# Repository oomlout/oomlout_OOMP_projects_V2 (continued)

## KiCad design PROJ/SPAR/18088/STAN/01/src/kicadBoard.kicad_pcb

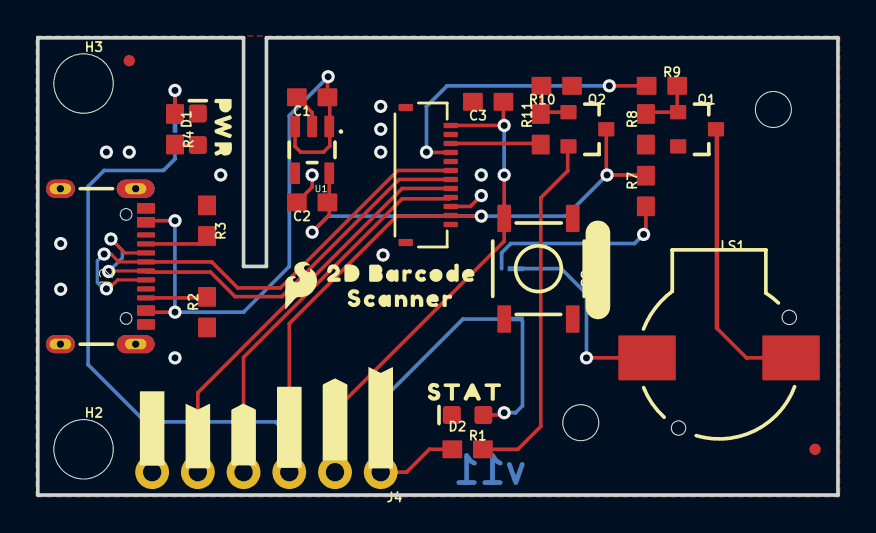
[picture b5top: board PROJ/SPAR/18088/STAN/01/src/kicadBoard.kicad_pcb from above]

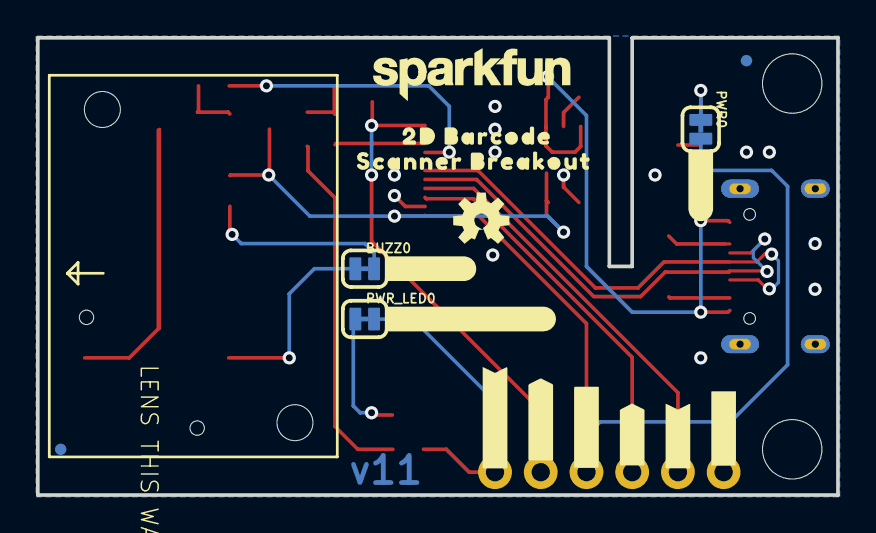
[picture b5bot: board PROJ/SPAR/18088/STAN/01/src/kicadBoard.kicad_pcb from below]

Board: 2 copper layers, 44.5 x 25.4 mm, 58 parts (19 on the bottom side), 22 nets.

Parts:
BUZZ0: JUMPER-SMT_2_NC_TRACE_SILK; SMT-JUMPER_2_NC_TRACE_SILK
C1, C2: 1.0uF; 0603
C3: 0.1uF; 0603
D1: RED; LED-0603
D2: GREEN; LED-0603
FD1, FD2, FD3, FD4: FIDUCIALUFIDUCIAL; FIDUCIAL-MICRO
FRAME1: FRAME-LETTER; CREATIVE_COMMONS
H2, H3: STAND-OFF
J2: USB-C-16P-2LAYER-PADS
J3: FPC_12_0.5MM
J4: 1X06_NO_SILK
LOGO1: OSHW-LOGOS; OSHW-LOGO-S
LOGO2: SFE_LOGO_FLAME.1_INCH; SFE_LOGO_FLAME_.1
LOGO3: SFE_LOGO_NAME.1_INCH; SFE_LOGO_NAME_.1
LS1: BUZZER-SMD; BUZZER-CCV
PWR0: JUMPER-SMT_2_NC_TRACE_SILK; SMT-JUMPER_2_NC_TRACE_SILK
PWR_LED0: JUMPER-SMT_2_NC_TRACE_SILK; SMT-JUMPER_2_NC_TRACE_SILK
Q1, Q2: 600mA/40V; SOT23-3
R1: 100; 0603
R2, R3: 5.1k; 0603
R4, R9, R11: 1k; 0603
R7: 10; 0603
R8, R10: 10k; 0603
S2: MOMENTARY-SWITCH-SPST-SMD-5.2MM-TALL; TACTILE_SWITCH_SMD_5.2MM
U1: 3.3V; SOT23-5
U2: BARCODE_SCANNER_MOUNT
U$1, U$7: ##TRIG##0
U$2, U$21: #STAT_#0
U$3: STAT0
U$4: #SCAN#0
U$5: #BUZZ#0
U$6: #STAT_LED#0
U$8: PWR0
U$9: #LED#0
U$17, U$18: 2D_BARCODE0
U$19: SCANNER0
U$20: SCANNER_BREAKOUT0
U$26, U$27: #TX_#0
U$28, U$29: #3#3V_#0
U$30, U$31: #RX_#0
U$32, U$33: #GND_#0

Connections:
3.3V: C2.1, J3.11, J4.3, PWR0.2, Q2.3, R7.2, U1.5
5V: C1.1, J2.VBUS1, J2.VBUS2, U1.1, U1.3
BUZZER: J3.4, R9.1
CC3: J2.A5, R3.2
CC4: J2.B5, R2.2
GND: C1.2, C2.2, C3.2, D1.C, D2.C, J2.GND, J2.GND2, J3.10, J4.6, Q1.2, R2.1, R3.1, R8.1, R10.1, S2.1, U1.2
unnamed: BUZZ0.2, R7.1
unnamed: LS1.-, Q1.3
unnamed: BUZZ0.1, LS1.+
unnamed: Q2.2, R1.2
unnamed: Q1.1, R8.2, R9.2
unnamed: PWR0.1, R4.1
unnamed: Q2.1, R10.2, R11.2
unnamed: D2.A, PWR_LED0.1
unnamed: D1.A, R4.2
RXI: J3.9, J4.4
STATUS_LED: J3.3, R11.1
STATUS_OUT: J4.1, PWR_LED0.2, R1.1
TXO: J3.8, J4.5
USB_N: J2.A7, J2.B7, J3.7
USB_P: J2.A6, J2.B6, J3.6
~SCAN_TRIGGER: C3.1, J3.1, J4.2, S2.3

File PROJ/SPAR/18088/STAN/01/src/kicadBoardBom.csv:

"Id";"Designator";"Package";"Quantity";"Designation";"Supplier and ref";
1;"Q1,Q2";"SOT23-3";2;"600mA/40V";;;
2;"R7";"0603";1;"10";;;
3;"LS1";"BUZZER-CCV";1;"BUZZER-SMD";;;
4;"R11,R9,R4";"0603";3;"1k";;;
5;"D2";"LED-0603";1;"GREEN";;;
6;"FD2,FD1,FD4,FD3";"FIDUCIAL-MICRO";4;"FIDUCIALUFIDUCIAL";;;
7;"D1";"LED-0603";1;"RED";;;
8;"R10,R8";"0603";2;"10k";;;
9;"C2,C1";"0603";2;"1.0uF";;;
10;"U$1,U$7";"##TRIG##0";2;"";;;
11;"U$8";"PWR0";1;"";;;
12;"J4";"1X06_NO_SILK";1;"";;;
13;"U$26,U$27";"#TX_#0";2;"";;;
14;"S2";"TACTILE_SWITCH_SMD_5.2MM";1;"MOMENTARY-SWITCH-SPST-SMD-5.2MM-TALL";;;
15;"R3,R2";"0603";2;"5.1k";;;
16;"J3";"FPC_12_0.5MM";1;"";;;
17;"U$4";"#SCAN#0";1;"";;;
18;"U$30,U$31";"#RX_#0";2;"";;;
19;"U$2,U$21";"#STAT_#0";2;"";;;
20;"J2";"USB-C-16P-2LAYER-PADS";1;"";;;
21;"U$32,U$33";"#GND_#0";2;"";;;
22;"H3,H2";"STAND-OFF";2;"STAND-OFF";;;
23;"U1";"SOT23-5";1;"3.3V";;;
24;"LOGO2";"SFE_LOGO_FLAME_.1";1;"SFE_LOGO_FLAME.1_INCH";;;
25;"C3";"0603";1;"0.1uF";;;
26;"U$17,U$18";"2D_BARCODE0";2;"";;;
27;"U$19";"SCANNER0";1;"";;;
28;"U$28,U$29";"#3#3V_#0";2;"";;;
29;"R1";"0603";1;"100";;;
30;"U$3";"STAT0";1;"";;;
31;"FRAME1";"CREATIVE_COMMONS";1;"FRAME-LETTER";;;
32;"PWR0,BUZZ0,PWR_LED0";"SMT-JUMPER_2_NC_TRACE_SILK";3;"JUMPER-SMT_2_NC_TRACE_SILK";;;
33;"LOGO1";"OSHW-LOGO-S";1;"OSHW-LOGOS";;;
34;"LOGO3";"SFE_LOGO_NAME_.1";1;"SFE_LOGO_NAME.1_INCH";;;
35;"U$9";"#LED#0";1;"";;;
36;"U$5";"#BUZZ#0";1;"";;;
37;"U$20";"SCANNER_BREAKOUT0";1;"";;;
38;"U$6";"#STAT_LED#0";1;"";;;
39;"U2";"BARCODE_SCANNER_MOUNT";1;"BARCODE_SCANNER_MOUNT";;;

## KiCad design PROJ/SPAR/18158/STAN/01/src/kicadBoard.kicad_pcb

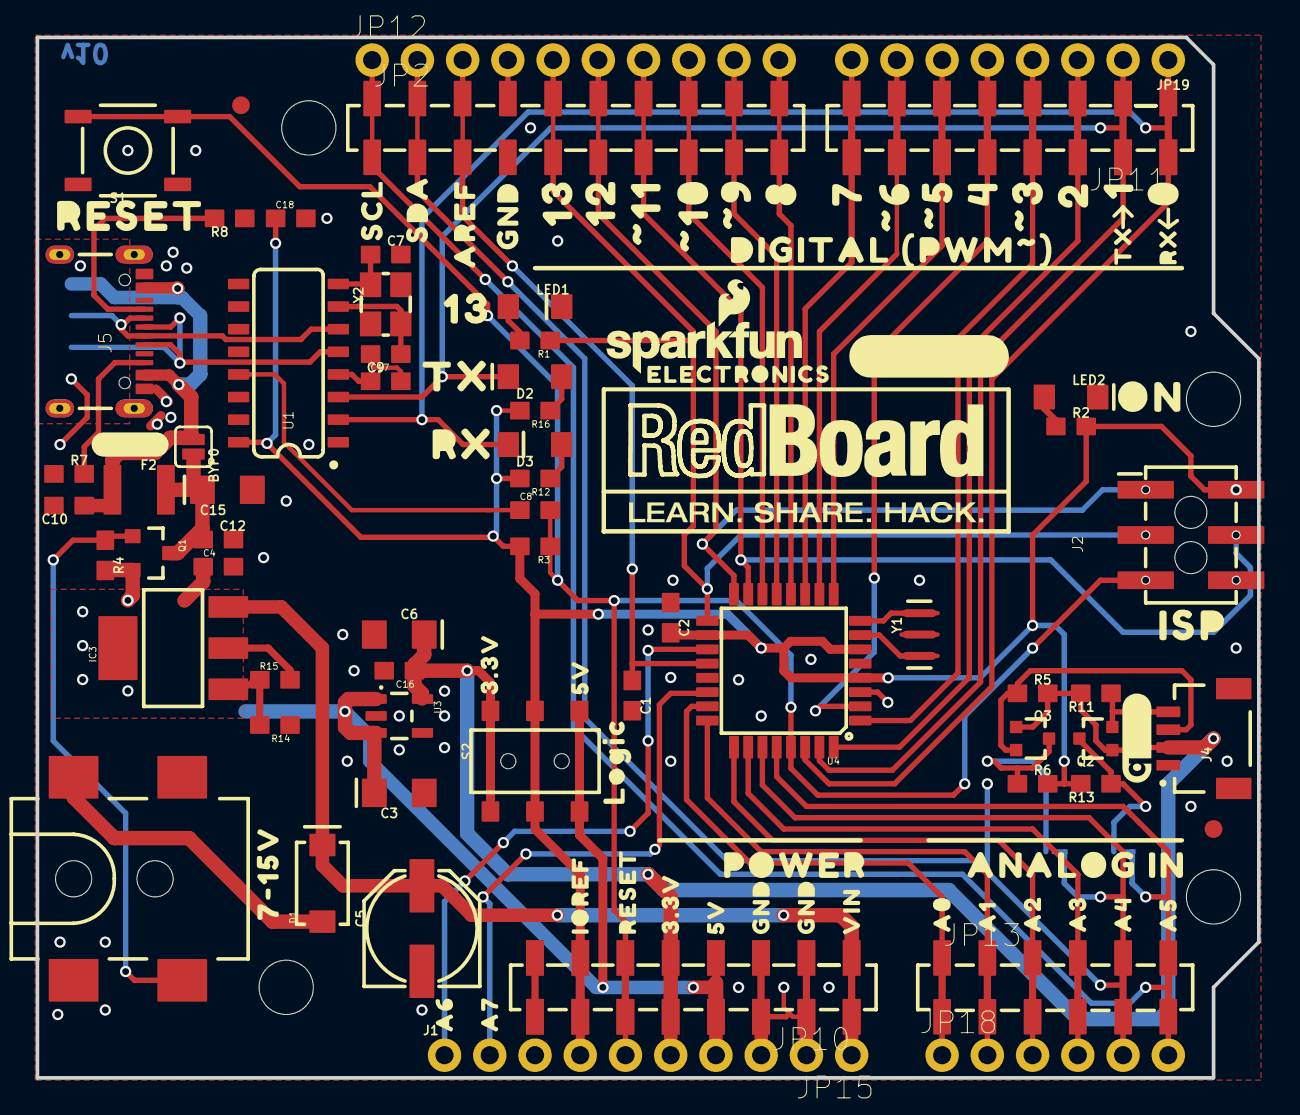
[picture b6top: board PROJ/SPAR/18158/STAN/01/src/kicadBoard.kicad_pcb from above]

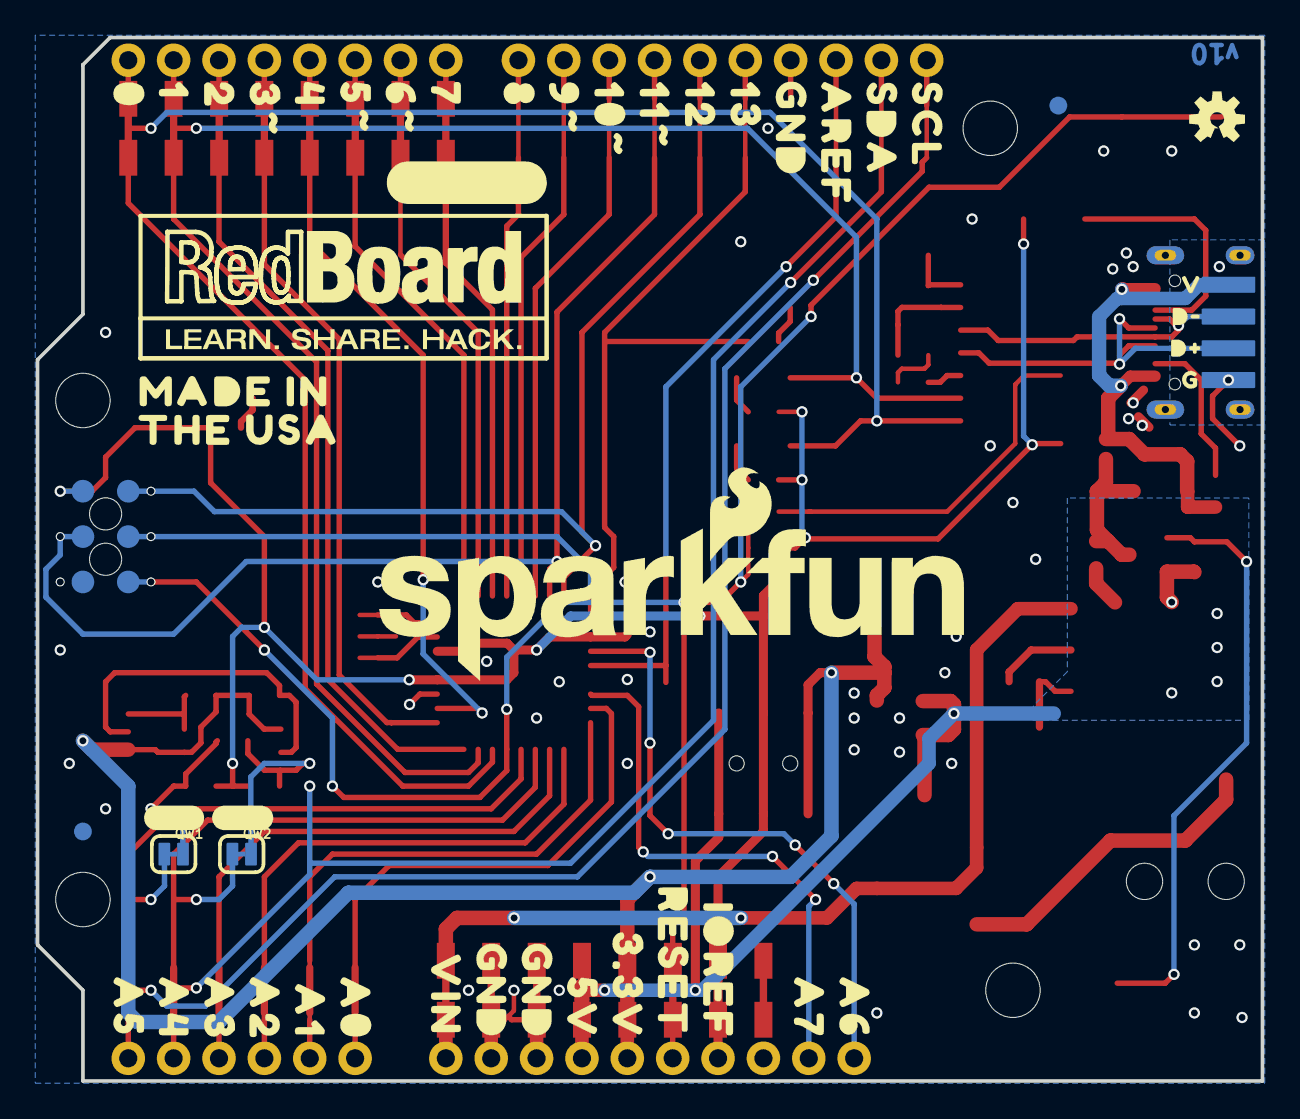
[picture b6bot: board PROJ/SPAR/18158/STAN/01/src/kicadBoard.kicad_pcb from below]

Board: 2 copper layers, 68.6 x 58.4 mm, 179 parts (57 on the bottom side), 53 nets.

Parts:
BYP0: JUMPER-SMT_2_NO_SILK; SMT-JUMPER_2_NO_SILK
C1, C2, C4, C8, C10, C12, C18: 0.1uF; 0603
C3, C6, C15: 10uF; EIA3216
C5: 47uF; PANASONIC_D
C7, C9: 10pF; 0603
C16: 1.0uF; 0603
C17: 10nF; 0603
D1: 1A/40V/500mV; SMA-DIODE
D2: GREEN; LED-1206
D3: YELLOW; LED-1206-HIDDENSILK
F2: 6V/2A; 1210
FD1, FD2: FIDUCIAL1X2; FIDUCIAL-1X2
FRAME1: FRAME-LEDGER; CREATIVE_COMMONS
IC3: LM1117; SOT223
J1: DNP; 1X02_NO_SILK
J2: ISP; 2X3_SMT_POSTS
J3: 5.5x2.1mm Barrel; POWER_JACK_SMD
J4: QWIIC_RIGHT_ANGLE; JST04_1MM_RA
J5: USB Female Type C Connector; USB-C-16P-2LAYER-PADS
JP1: SFE_LOGO_NAME.1_INCH; SFE_LOGO_NAME_.1
JP2: 1X10_SMD_COMBINED
JP3, JP4, JP5, JP6: STAND-OFFTIGHT; STAND-OFF-TIGHT
JP7: SFE_LOGO_FLAME.1_INCH; SFE_LOGO_FLAME_.1
JP8, JP9: FIDUCIAL1X2; FIDUCIAL-1X2
JP10: 1X08_SMD_COMBINED
JP11: JP11; 1X08_SMD_COMBINED
JP12: DNP; 1X10_NO_SILK
JP13: 1X06_SMD_STRAIGHT_COMBO
JP14: USB_SOLDER_PADS; USB-SOLDER-PADS
JP15, JP19: DNP; 1X08_NO_SILK
JP18: DNP; 1X06_NO_SILK
LED1: Blue; LED-1206-HIDDENSILK
LED2: GREEN; LED-1206
LOGO1: QWIIC_LOGO_5MM; QWIIC_5MM
Q1: 20V/4.2A/52mΩ/1.4W; SOT23-3
Q2, Q3: 310mA/60V/1.6Ω; SOT323
QW1, QW2: JUMPER-SMT_2_NC_TRACE_SILK; SMT-JUMPER_2_NC_TRACE_SILK
R1, R12, R16: 4.7k; 0603
R2, R3, R4: 10k; 0603
R5, R6, R11, R13: 2.2k; 0603
R7, R8: 5.1k; 0603
R14: 715; 0603
R15: 240; 0603
S1: Tall Switch; TACTILE_SWITCH_SMD_5.2MM
S2: SWITCH_DPDT_SMD_AYZ0202
TP1, TP2, TP3, TP4, TP5, TP6: TP-3x5; PAD.03X.05
U1: CH340G; SO016
U3: 3.3V; SOT23-5
U4: ATMEGA328P_TQFP; TQFP32-08
U$1, U$3: REDBOARD_LOGO
U$2: _D#0
U$4: V0
U$9: 10#0
U$10: G0
U$11: LOGIC0
U$12: D#0
U$13, U$95: _RESET0
U$14: #BYP#0
U$16: OSHW-LOGOS; OSHW-LOGO-S
U$17: 7#15V0
U$18: _AREF0
U$19: _SCL0
U$20: _SDA0
U$21: 11#0
U$22, U$77: 130
U$23, U$76: 120
U$24: #110
U$25: #100
U$26: #90
U$27, U$72: 80
U$28, U$71: 70
U$29: #60
U$30: #50
U$31, U$68: 40
U$32: #30
U$33, U$66: 20
U$34, U$65: 10
U$35, U$64: 00
U$36: TX0
U$37: RX0
U$38: DIGITAL_##PWM####_0
U$39: 13_0
U$40: _TX0
U$41: _RX0
U$42: _GND0
U$43, U$51: 3#3V0
U$44, U$52: 5V0
U$45: ON0
U$46: ISP0
U$47: POWER0
U$48: ANALOG_IN0
U$49: IOREF0
U$50: RESET0
U$53, U$54: GND0
U$55: VIN0
U$56: A00
U$57: A10
U$58: A20
U$59: A30
U$60: A40
U$61: A50
U$62: A60
U$63: A70
U$67: 3#0
U$69: 5#0
U$70: 6#0
U$73: 9#0
U$78: SFE_LOGO_NAME_.3
U$79: AREF0
U$80: SDA0
U$81: SCL0
U$82: MADE_IN0
U$83: THE_USA0
U$84: _A40
U$85, U$99, U$107: _GND_0
U$86: _A30
U$87: _A20
U$88: _A10
U$89: _A00
U$90: _VIN0
U$93: _5V0
U$94: _3#3V0
U$96: _IOREF0
U$97: _A60
U$98: _A70
U$100, U$103: #PLUS#0
U$101: SFE_LOGO_FLAME_.2
U$102: _A50
U$104: ELECTRONICS0
U$105: #A4#0
U$106: #A5#0
Y1: 16MHz; RESONATOR-SMD-3.2X1.3
Y2: 12MHz; CRYSTAL-SMD-3.2X2.5MM

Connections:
3.3V: C6.+, C16.1, J4.2, JP10.5, JP15.5, Q2.1, Q3.1, R5.2, R11.2, S2.1, S2.4, U3.5
5V: C3.+, C4.1, IC3.2, IC3.4, JP10.4, JP15.4, Q1.2, R4.2, R15.2, S2.3, S2.6, U3.1, U3.3
A0: JP13.1, JP18.1, U4.23
A1: JP13.2, JP18.2, U4.24
A2: JP13.3, JP18.3, U4.25
A3: JP13.4, JP18.4, U4.26
A4/SDA: JP2.2A, JP2.2B, JP12.2, JP13.5, JP18.5, QW2.1, U4.27
A5/SCL: JP2.1A, JP2.1B, JP12.1, JP13.6, JP18.6, QW1.1, U4.28
A6: J1.1, U4.19
A7: J1.2, U4.22
AREF: C1.1, JP2.3A, JP2.3B, JP12.3, U4.20
CC1: J5.A5, R8.2
CC2: J5.B5, R7.2
CIPO: J2.1, JP2.6A, JP2.6B, JP12.6, TP4.P$1, U4.16
COPI: J2.4, JP2.7A, JP2.7B, JP12.7, TP2.P$1, U4.15
D2: JP11.3, JP19.3, U4.32
D3: JP11.4, JP19.4, U4.1
D4: JP11.5, JP19.5, U4.2
D5: JP11.6, JP19.6, U4.9
D6: JP11.7, JP19.7, U4.10
D7: JP11.8, JP19.8, U4.11
D8: JP2.10A, JP2.10B, JP12.10, U4.12
D9: JP2.9A, JP2.9B, JP12.9, U4.13
D10: JP2.8A, JP2.8B, JP12.8, U4.14
D+: J5.A6, J5.B6, JP14.D+, U1.5
D-: J5.A7, J5.B7, JP14.D-, U1.6
GND: C1.2, C2.1, C3.-, C4.2, C5.-, C6.-, C7.2, C9.2, C10.2, C12.2, C15.-, C16.2, C17.2, C18.2, J2.6, J3.GND, J4.1, J5.GND, J5.GND2, JP2.4A, JP2.4B, JP10.2, JP10.3, JP12.4, JP14.GND, JP15.2, JP15.3, LED1.C, LED2.C, R7.1, R8.1, R14.1, S1.1, S1.2, TP3.P$1, U1.1, U3.2, U4.3, U4.5, U4.21, Y1.2, Y2.2, Y2.4
INSERT: J3.P$4, Q1.1, R4.1
LV_SCL: J4.4, Q2.2, R11.1
LV_SDA: J4.3, Q3.2, R5.1
unnamed: LED1.A, R1.2
unnamed: LED2.A, R2.1
unnamed: U4.7, Y1.1
unnamed: U4.8, Y1.3
unnamed: D2.A, R16.1
unnamed: C17.1, U1.4
unnamed: Q2.3, QW1.2, R13.1
unnamed: C9.1, U1.7, Y2.1
unnamed: D3.A, R12.1
unnamed: C7.1, U1.8, Y2.3
unnamed: IC3.1, R14.2, R15.1
unnamed: Q3.3, QW2.2, R6.1
PWRIN: D1.A, J3.VIN0
RX-I: D3.C, JP11.1, JP19.1, U1.2, U4.30
SCK: J2.3, JP2.5A, JP2.5B, JP12.5, R1.1, TP5.P$1, U4.17
SHLD: J5.SHLD1, J5.SHLD2, J5.SHLD3, J5.SHLD4
TX-O: D2.C, JP11.2, JP19.2, U1.3, U4.31
USBVCC: BYP0.2, C12.1, C15.+, F2.2, Q1.3
VCC: C2.2, C18.1, J2.2, JP10.7, JP15.7, R2.2, R3.2, R6.2, R12.2, R13.2, R16.2, S2.2, S2.5, TP1.P$1, U1.16, U4.4, U4.6, U4.18
VIN: C5.+, D1.C, IC3.3, JP10.1, JP15.1
VUSB: BYP0.1, C10.1, F2.1, J5.VBUS1, J5.VBUS2, JP14.VBUS
~DTR: C8.1, U1.13
~RESET: C8.2, J2.5, JP10.6, JP15.6, R3.1, S1.3, S1.4, TP6.P$1, U4.29

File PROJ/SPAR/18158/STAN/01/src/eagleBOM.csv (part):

"Part";"Value";"Device";"Package";"Description";"DESIGNER";"PROD_ID";"REV";"SF_ID";"SF_SKU";"VALUE";
"BYP";"JUMPER-SMT_2_NO_SILK";"JUMPER-SMT_2_NO_SILK";"SMT-JUMPER_2_NO_SILK";"Normally open jumper";"";"";"";"";"";"";
"C1";"0.1uF";"0.1UF-0603-25V-(+80/-20%)";"0603";"0.1µF ceramic capacitors";"";"CAP-00810";"";"";"";"0.1uF";
"C2";"0.1uF";"0.1UF-0603-25V-(+80/-20%)";"0603";"0.1µF ceramic capacitors";"";"CAP-00810";"";"";"";"0.1uF";
"C3";"10uF";"10UF-POLAR-EIA3216-16V-10%(TANT)";"EIA3216";"10.0µF polarized capacitors";"";"CAP-00811";"";"";"";"10uF";
"C4";"0.1uF";"0.1UF-0603-25V-(+80/-20%)";"0603";"0.1µF ceramic capacitors";"";"CAP-00810";"";"";"";"0.1uF";
"C5";"47uF";"47UF-POLAR-PANASONIC_D-35V-20%";"PANASONIC_D";"47µF polarized capacitors";"";"CAP-08478";"";"";"";"47uF";
"C6";"10uF";"10UF-POLAR-EIA3216-16V-10%(TANT)";"EIA3216";"10.0µF polarized capacitors";"";"CAP-00811";"";"";"";"10uF";
"C7";"10pF";"10PF-0603-50V-5%";"0603";"10pF ceramic capacitors";"";"CAP-11812";"";"";"";"10pF";
"C8";"0.1uF";"0.1UF-0603-25V-(+80/-20%)";"0603";"0.1µF ceramic capacitors";"";"CAP-00810";"";"";"";"0.1uF";
"C9";"10pF";"10PF-0603-50V-5%";"0603";"10pF ceramic capacitors";"";"CAP-11812";"";"";"";"10pF";
"C10";"0.1uF";"0.1UF-0603-25V-(+80/-20%)";"0603";"0.1µF ceramic capacitors";"";"CAP-00810";"";"";"";"0.1uF";
"C12";"0.1uF";"0.1UF-0603-25V-(+80/-20%)";"0603";"0.1µF ceramic capacitors";"";"CAP-00810";"";"";"";"0.1uF";
"C15";"10uF";"10UF-POLAR-EIA3216-16V-10%(TANT)";"EIA3216";"10.0µF polarized capacitors";"";"CAP-00811";"";"";"";"10uF";
"C16";"1.0uF";"1.0UF-0603-16V-10%";"0603";"1µF ceramic capacitors";"";"CAP-00868";"";"";"";"1.0uF";
"C17";"10nF";"10NF-0603-50V-10%";"0603";"0.01uF/10nF/10,000pF ceramic capacitors";"";"CAP-00867";"";"";"";"10nF";
"C18";"0.1uF";"0.1UF-0603-25V-(+80/-20%)";"0603";"0.1µF ceramic capacitors";"";"CAP-00810";"";"";"";"0.1uF";
"D1";"1A/40V/500mV";"DIODE-SCHOTTKY-SS14";"SMA-DIODE";"Schottky diode";"";"DIO-08053";"";"";"";"1A/40V/500mV";
"D2";"GREEN";"LED-GREENLILYPAD";"LED-1206";"Green SMD LED";"";"DIO-09910";"";"";"";"GREEN";
"D3";"YELLOW";"LED-YELLOW_HIDDENSILK";"LED-1206-HIDDENSILK";"Yellow SMD LED";"";"DIO-09909";"";"";"";"YELLOW";
"F2";"6V/2A";"PPTC_6V2A";"1210";"Resettable Fuse PPTC";"";"RES-14313";"";"";"";"6V/2A";
"FD1";"FIDUCIAL1X2";"FIDUCIAL1X2";"FIDUCIAL-1X2";"Fiducial Alignment Points";"";"";"";"";"";"";
"FD2";"FIDUCIAL1X2";"FIDUCIAL1X2";"FIDUCIAL-1X2";"Fiducial Alignment Points";"";"";"";"";"";"";
"FRAME1";"FRAME-LEDGER";"FRAME-LEDGER";"CREATIVE_COMMONS";"Schematic Frame - Ledger";"";"";"";"";"";"";
"IC3";"LM1117";"V_REG_LM1117SOT223";"SOT223";"Voltage Regulator LM1117";"";"VREG-08170";"";"";"";"";
"J1";"DNP";"CONN_021X02_NO_SILK";"1X02_NO_SILK";"Multi connection point. Often used as Generic Header-pin footprint for 0.1 inch spaced/style header connections";"";"";"";"";"";"";
"J2";"ISP";"AVR_SPI_PROG_3X2SMD";"2X3_SMT_POSTS";"AVR ISP 6 Pin";"";"CONN-11415";"";"";"";"";
"J3";"5.5x2.1mm Barrel";"POWER_JACKSMD";"POWER_JACK_SMD";"Power Jack Connector";"";"CONN-08106";"";"PRT-12748";"";"5.5x2.1mm Barrel";
"J4";"QWIIC_RIGHT_ANGLE";"QWIIC_CONNECTORJS-1MM";"JST04_1MM_RA";"SparkFun I2C Standard Qwiic Connector";"";"CONN-13694";"";"";"";"QWIIC_RIGHT_ANGLE";
"J5";"USB Female Type C Connector";"USB_C_2-LAYER_PADS";"USB-C-16P-2LAYER-PADS";"USB Type C 16Pin Connector";"";"CONN-14122";"";"";"";"";
"JP1";"SFE_LOGO_NAME.1_INCH";"SFE_LOGO_NAME.1_INCH";"SFE_LOGO_NAME_.1";"SparkFun Font Logo";"";"";"";"";"";"";
"JP2";"";"CONN_10SMD_COMBO-FEMALE";"1X10_SMD_COMBINED";"Multi connection point. Often used as Generic Header-pin footprint for 0.1 inch spaced/style header connections";"";"CONN-11219";"";"";"";"";
"JP3";"STAND-OFFTIGHT";"STAND-OFFTIGHT";"STAND-OFF-TIGHT";"Stand Off";"";"";"";"";"";"";
"JP4";"STAND-OFFTIGHT";"STAND-OFFTIGHT";"STAND-OFF-TIGHT";"Stand Off";"";"";"";"";"";"";
"JP5";"STAND-OFFTIGHT";"STAND-OFFTIGHT";"STAND-OFF-TIGHT";"Stand Off";"";"";"";"";"";"";
"JP6";"STAND-OFFTIGHT";"STAND-OFFTIGHT";"STAND-OFF-TIGHT";"Stand Off";"";"";"";"";"";"";
"JP7";"SFE_LOGO_FLAME.1_INCH";"SFE_LOGO_FLAME.1_INCH";"SFE_LOGO_FLAME_.1";"SparkFun Flame Logo";"";"";"";"";"";"";
"JP8";"FIDUCIAL1X2";"FIDUCIAL1X2";"FIDUCIAL-1X2";"Fiducial Alignment Points";"";"";"";"";"";"";
"JP9";"FIDUCIAL1X2";"FIDUCIAL1X2";"FIDUCIAL-1X2";"Fiducial Alignment Points";"";"";"";"";"";"";
"JP10";"";"CONN_08SMD-COMBO-FEMALE";"1X08_SMD_COMBINED";"Multi connection point. Often used as Generic Header-pin footprint for 0.1 inch spaced/style header connections";"";"CONN-10204";"";"PRT-11543";"";"";
"JP11";"JP11";"CONN_08SMD-COMBO-FEMALE";"1X08_SMD_COMBINED";"Multi connection point. Often used as Generic Header-pin footprint for 0.1 inch spaced/style header connections";"";"CONN-10204";"";"PRT-11543";"";"";
"JP12";"DNP";"CONN_10NO_SILK_PTH_FEMALE";"1X10_NO_SILK";"Multi connection point. Often used as Generic Header-pin footprint for 0.1 inch spaced/style header connections";"";"CONN-11219";"";"";"";"";
"JP13";"";"CONN_06SMD-STRAIGHT-COMBO-FEMALE";"1X06_SMD_STRAIGHT_COMBO";"Multi connection point. Often used as Generic Header-pin footprint for 0.1 inch spaced/style header connections";"";"CONN-10203";"";"";"";"";
"JP14";"USB_SOLDER_PADS";"USB_SOLDER_PADS";"USB-SOLDER-PADS";"Solder pad access to USB pins. Helpful to expose on PCBs so user can attach external USB connector if necessary.";"";"";"";"";"";"";
"JP15";"DNP";"CONN_08NO_SILK_DNP";"1X08_NO_SILK";"Multi connection point. Often used as Generic Header-pin footprint for 0.1 inch spaced/style header connections";"";"CONN-10204";"";"";"";"";
"JP18";"DNP";"CONN_06NO_SILK_NO_POP";"1X06_NO_SILK";"Multi connection point. Often used as Generic Header-pin footprint for 0.1 inch spaced/style header connections";"";"CONN-10203";"";"";"";"";
"JP19";"DNP";"CONN_08NO_SILK_DNP";"1X08_NO_SILK";"Multi connection point. Often used as Generic Header-pin footprint for 0.1 inch spaced/style header connections";"";"";"";"";"";"";
"LED1";"Blue";"LED-BLUE_HIDDENSILK";"LED-1206-HIDDENSILK";"Blue SMD LED";"";"DIO-09911";"";"";"";"";
"LED2";"GREEN";"LED-GREENLILYPAD";"LED-1206";"Green SMD LED";"";"DIO-09910";"";"";"";"GREEN";
"LOGO1";"QWIIC_LOGO_5MM";"QWIIC_LOGO_5MM";"QWIIC_5MM";"Qwiic Logos for placement on schematic and PCB. The 5.5mm silk logo is best for placing next to Qwiic connector.";"";"";"";"";"";"";
"Q1";"20V/4.2A/52mΩ/1.4W";"MOSFET_PCH-DMG2305UX-7";"SOT23-3";"P-channel MOSFETs";"";"TRANS-14388";"";"";"";"20V/4.2A/52mΩ/1.4W";
"Q2";"310mA/60V/1.6Ω";"MOSFET-NCH-2N7002PW";"SOT323";"N-channel MOSFETs";"";"TRANS-11151";"";"";"";"310mA/60V/1.6Ω";
"Q3";"310mA/60V/1.6Ω";"MOSFET-NCH-2N7002PW";"SOT323";"N-channel MOSFETs";"";"TRANS-11151";"";"";"";"310mA/60V/1.6Ω";
"QW1";"JUMPER-SMT_2_NC_TRACE_SILK";"JUMPER-SMT_2_NC_TRACE_SILK";"SMT-JUMPER_2_NC_TRACE_SILK";"Normally closed trace jumper";"";"";"";"";"";"";
"QW2";"JUMPER-SMT_2_NC_TRACE_SILK";"JUMPER-SMT_2_NC_TRACE_SILK";"SMT-JUMPER_2_NC_TRACE_SILK";"Normally closed trace jumper";"";"";"";"";"";"";
"R1";"4.7k";"4.7KOHM-0603-1/10W-1%";"0603";"4.7kΩ resistor";"";"RES-07857";"";"";"";"4.7k";
"R2";"10k";"10KOHM-0603-1/10W-1%";"0603";"10kΩ resistor";"";"RES-00824";"";"";"";"10k";
"R3";"10k";"10KOHM-0603-1/10W-1%";"0603";"10kΩ resistor";"";"RES-00824";"";"";"";"10k";
"R4";"10k";"10KOHM-0603-1/10W-1%";"0603";"10kΩ resistor";"";"RES-00824";"";"";"";"10k";
"R5";"2.2k";"2.2KOHM-0603-1/10W-1%";"0603";"2.2kΩ resistor";"";"RES-08272";"";"";"";"2.2k";
"R6";"2.2k";"2.2KOHM-0603-1/10W-1%";"0603";"2.2kΩ resistor";"";"RES-08272";"";"";"";"2.2k";
"R7";"5.1k";"5.1KOHM5.1KOHM-0603-1/10W-1%";"0603";"";"";"RES-12083";"";"";"";"5.1k";
"R8";"5.1k";"5.1KOHM5.1KOHM-0603-1/10W-1%";"0603";"";"";"RES-12083";"";"";"";"5.1k";
"R11";"2.2k";"2.2KOHM-0603-1/10W-1%";"0603";"2.2kΩ resistor";"";"RES-08272";"";"";"";"2.2k";
"R12";"4.7k";"4.7KOHM-0603-1/10W-1%";"0603";"4.7kΩ resistor";"";"RES-07857";"";"";"";"4.7k";
"R13";"2.2k";"2.2KOHM-0603-1/10W-1%";"0603";"2.2kΩ resistor";"";"RES-08272";"";"";"";"2.2k";
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
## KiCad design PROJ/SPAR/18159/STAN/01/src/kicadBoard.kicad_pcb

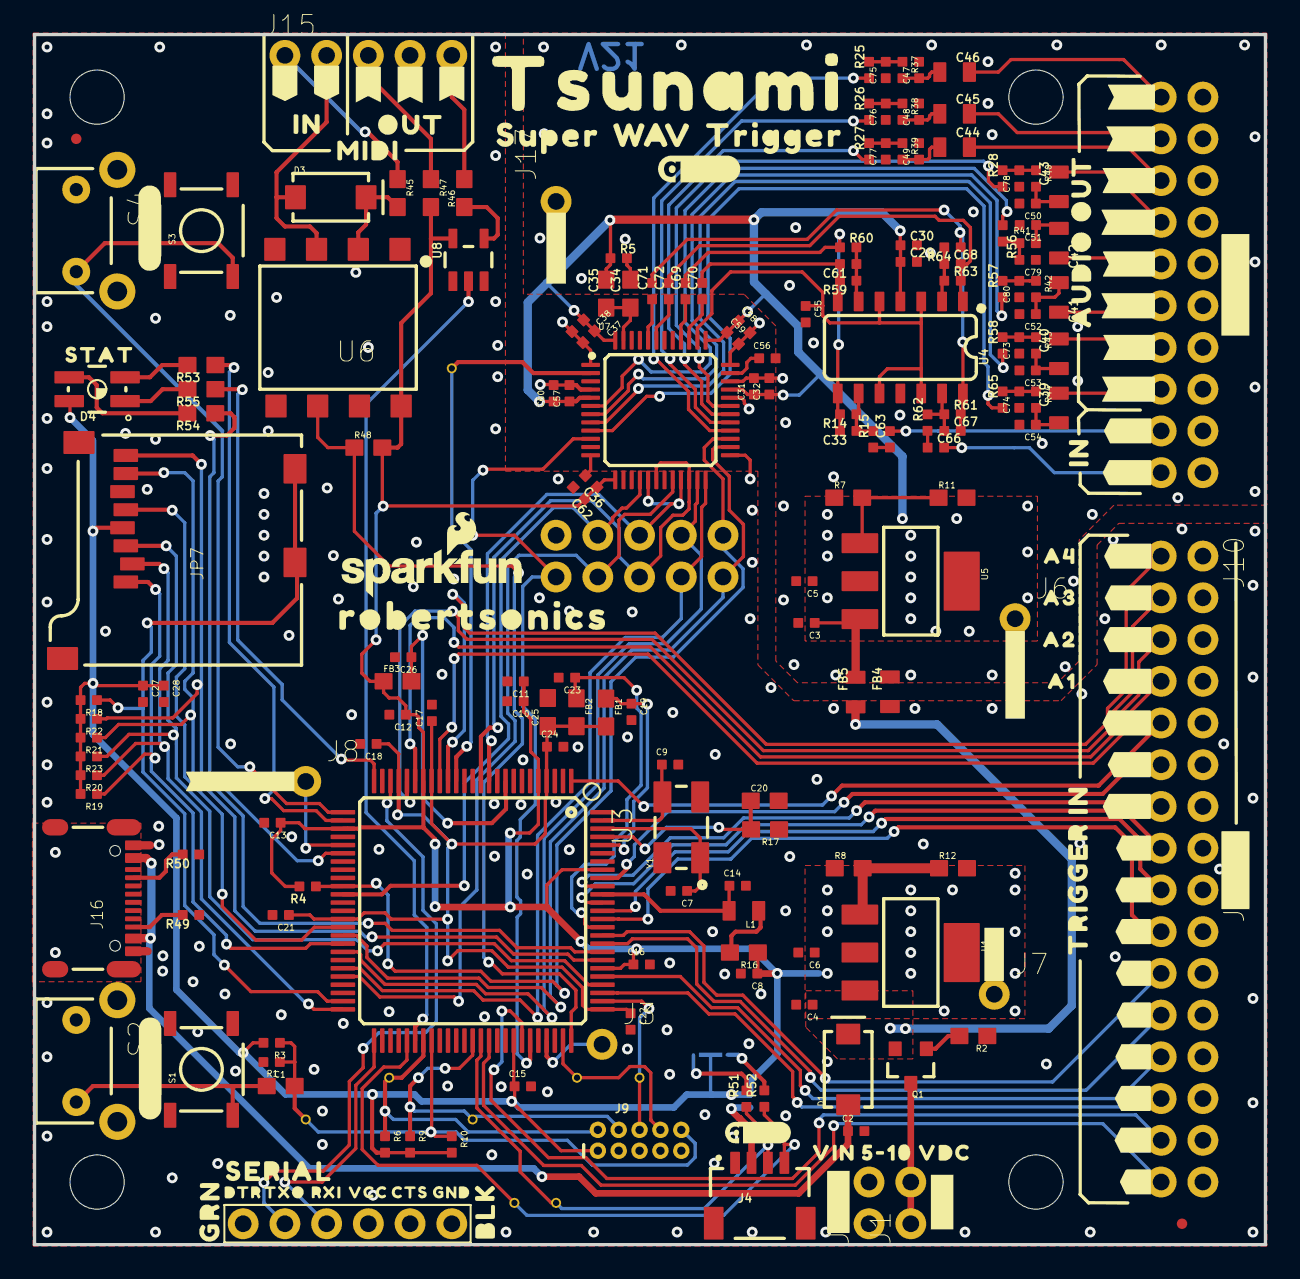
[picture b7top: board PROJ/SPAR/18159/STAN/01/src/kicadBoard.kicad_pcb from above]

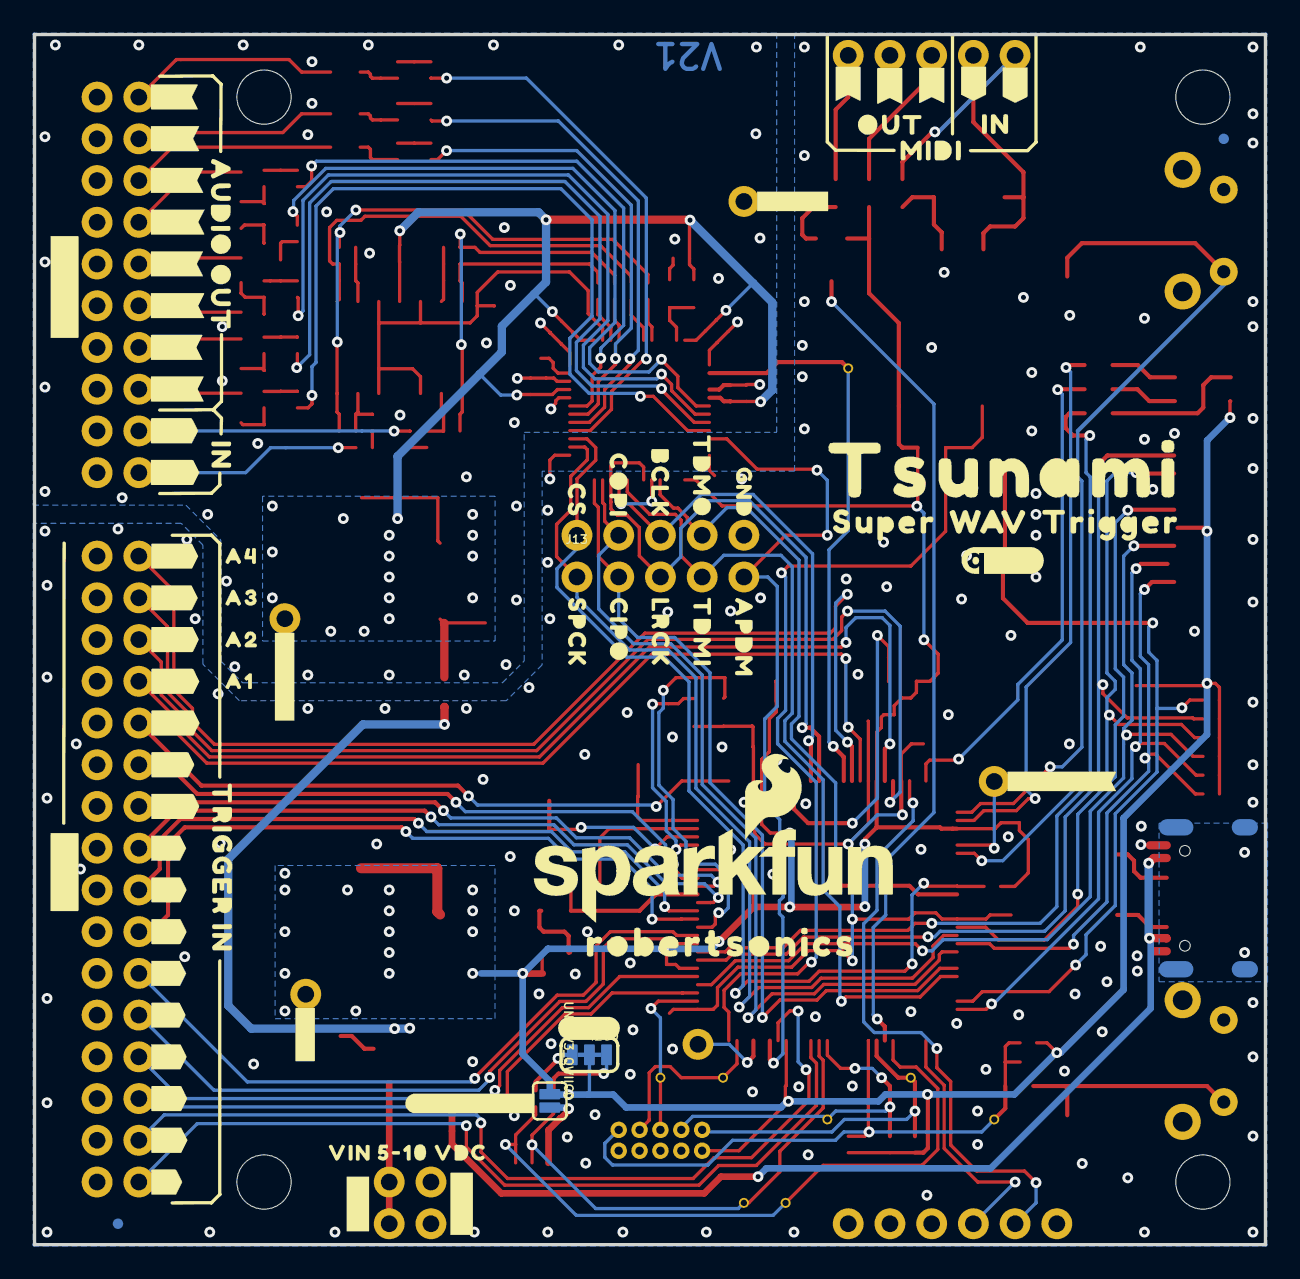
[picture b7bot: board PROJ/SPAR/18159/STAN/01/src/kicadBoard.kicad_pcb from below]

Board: 2 copper layers, 74.9 x 73.7 mm, 327 parts (76 on the bottom side), 138 nets.

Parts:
C1: 10nF; 0402-TIGHT
C2, C5, C6, C11, C27: 10uF; 0402-TIGHT
C3, C4, C8, C10, C12, C13, C15, C16, C17, C18, C19, C21, C22, C23, C24, C26, C28, C29, C31, C36, C37, C47, C48, C49, C50, C51, C52, C53, C54, C55, C56, C57, C59, C73, C74, C75, C76, C77, C78, C79, C80: 0.1uF; 0402-TIGHT
C7, C9: 12pF; 0402-TIGHT
C14: 4.7uF; 0402-TIGHT
C20: 10pF; 0603
C25: 2.2uF; 0603
C30, C32, C38, C58, C60, C62, C63, C66, C69, C70, C71, C72: 1.0uF; 0402-TIGHT
C33, C61, C67, C68: 100pF; 0402-TIGHT
C34: 5.6nF; 0603
C35: 390nF; 0603
C39, C40, C41, C42, C43, C44, C45, C46: 22uF; 0805
D1, D3: 1A/40V/500mV; SMA-DIODE
D4: RGB; P-LCC-4-3
FB1, FB2, FB3: 470Ω; 0603
FB4, FB5: 600Ω; 0805
FD1, FD2, FD3, FD4: FIDUCIALUFIDUCIAL; FIDUCIAL-MICRO
FRAME1, FRAME2: FRAME-LEDGER; CREATIVE_COMMONS
H1, H2, H3, H4: STAND-OFF
I2C0: SMT-JUMPER_3_2-NC_TRACE_SILK
J1: VDC-IN; 1X02_NO_SILK
J2: GND-IN; 1X02_NO_SILK
J3: DEBUG; 1X01_NO_SILK
J4: QWIIC; JST04_1MM_RA
J6: 3.3VA; 1X01_NO_SILK
J7: 3.3V; 1X01_NO_SILK
J8: PLAYING; 1X01_NO_SILK
J9: CORTEX_JTAG_DEBUG_PTH_NS; 2X5-PTH-1.27MM-NO_SILK
J10: TRIG2; 2X8_NOSILK
J11: TRIG1; 2X8_NOSILK
J13: 2X5_NOSILK
J14: AUDIO I/O; 2X10_NOSILK
J15: MIDI; 1X05_NO_SILK
J16: USB-C; USB-C-16P-4LAYER-ISOLATED
J17: AGND; 1X01_NO_SILK
J18: 6_PIN_SERIAL_TARGET_SIDE_W_SILK
JP7: USD-SOCKETNEW; MICRO-SD-SOCKET-PP
L1: 10μH; 0805
LOGO2: SFE_LOGO_NAME_FLAME.2_INCH; SFE_LOGO_NAME_FLAME_.2
LOGO3: QWIIC_LOGO_4MM; QWIIC_4MM
Q1: 3.1A/30V/105mΩ; SOT23-3
R1: 33; 0603
R2: 1M; 0603
R3, R4, R18, R23: 10k; 0402-TIGHT
R5: 560Ω; 0402-TIGHT
R6, R9, R10, R19, R20, R21, R22: 100k; 0402-TIGHT
R7, R8: 390; 0603
R11, R12: 240; 0603
R14, R15, R59, R60, R61, R62, R63, R64: 33k; 0402-TIGHT
R16: 2.2; 0603
R17: 5.62k; 0603
R25, R26, R27, R28, R37, R38, R39, R40, R41, R42, R43, R44, R56, R57, R58, R65: 10Ω; 0402-TIGHT
R45, R46, R47, R48, R55: 220; 0603
R49, R50: 5.1k; 0402-TIGHT
R51, R52: 2.2k; 0402-TIGHT
R53, R54: 100; 0603
S1: Reset; TACTILE_SWITCH_SMD_5.2MM
S2, S4: DNP; TACTILE_SWITCH_PTH_RIGHT_ANGLE
S3: User; TACTILE_SWITCH_SMD_5.2MM
TP1: I2C_SCK; TP_15TH
TP2: I2C_SDA; TP_15TH
TP4: MCLK; TP_15TH
TP5: SWDIO/TMS; TP_15TH
TP6: SWCK/TCK; TP_15TH
TP7: TDO; TP_15TH
TP8: TDI; TP_15TH
TP9: NRESET; TP_15TH
U1, U5: LM1117; SOT223
U3: ATSAMS70N20A-AN; LQFP100
U4: LMV324; SO14
U6: 6N138M; 8-SMD
U7: ADAU1328; LQFP-48
U8: 74AHC1G125W5-7; SOT23-5
U$3: GND_0
U$4, U$73: QWIIC_5MM
U$5: STAT0
U$6: #USER#0
U$7: #RESET#0
U$8, U$9: ROBERTSONICS0
U$10, U$167: #2L#0
U$11: #1L#0
U$12, U$120: #1R#0
U$13: #2R#0
U$14: #3R#0
U$15: #3L#0
U$16: #4L#0
U$17: #4R#0
U$18: #4#3
U$19: #2#5
U$20, U$107: AUDIO_OUT0
U$21, U$46, U$108, U$123: IN0
U$22, U$106: TRIGGER_IN0
U$23, U$85: #GND#0
U$24: #1#0
U$25: SERIAL3
U$26, U$60: SUPER0
U$27, U$99: VIN_5#10_VDC0
U$28, U$84: #AGND#0
U$29: #2#0
U$30: #3#0
U$31, U$56, U$117: #4#0
U$32, U$58, U$118: #5#0
U$33: #6#0
U$34: #7#0
U$35: #8#0
U$36: #9#0
U$37: #10#0
U$38: #11#0
U$39: #12#0
U$40: #PLAYING#30
U$41, U$112: #3V3#0
U$43: #13#0
U$44: #3V3_A#0
U$45, U$122: MIDI0
U$47, U$124: OUT0
U$48: #14#0
U$49: #15#0
U$50: #16#0
U$51: A10
U$52: A20
U$53: A30
U$54: A40
U$55: #5#6
U$57: #2#6
U$59: #4#6
U$61, U$110: #GND#1
U$62, U$68: TRIGGER0
U$63, U$69: TSUNAMI0
U$64, U$70: W0
U$65, U$71: A0
U$66, U$72: V0
U$67, U$111: #VIN#2
U$74: #16#5
U$75: #15#17
U$76: #14#17
U$77: #13#17
U$78: #12#17
U$79: #11#17
U$80: #10#17
U$81: #9#17
U$82: #8#17
U$83: #7#17
U$86: CS17
U$87: BCLK19
U$88: COPI18
U$89: TDMO20
U$91: SPCK22
U$92: TDMI25
U$93: LRCK24
U$94: CIPO23
U$95: APDM26
U$96: #AGND#27
U$97: #AGND#28
U$98: #PLAYING#29
U$102: A117
U$103: A2118
U$104: A32119
U$105: A432120
U$113: #I2C#6
U$116: #1L#3
U$119: #1L#6
U$121: #1R#2
U$141: SFE_LOGO_NAME_FLAME_.1
U$162: #3V3_A#4
U$163: #3V3_QWIIC#0
U$164: #1R#3
U$165: #5#5
U$166: #1L#2
U$168: #2R#3
U$169: #3L#3
U$170: #3R#4
U$171: #4L#4
U$172: #4R#5
U$173: #6#17
U$174: #5#17
U$175: #4#17
U$176: #3#17
U$177: #2#17
U$178: #1#17
UNK3V3_QWIIC0: SMT-JUMPER_2_NO_SILK
Y1: 11.2896 MHz; CRYSTAL-OSC-SMD-5X3

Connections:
3.3V: C6.1, C8.1, C10.1, C11.1, C12.1, C13.1, C15.1, C16.1, C27.1, C28.1, C36.1, C62.1, D4.4, FB3.1, I2C0.2, J7.1, J9.1, JP7.VCC, R3.2, R4.2, R6.2, R9.2, R10.2, R12.2, R16.1, R18.2, R19.2, R20.2, R21.2, R22.2, R23.2, R47.2, R48.2, U1.2, U1.4, U3.5, U3.19, U3.28, U3.68, U3.81, U3.93, U6.8, U7.13, U8.5, UNK3V3_QWIIC0.1
56: D3.C, R45.2, U6.2
ADC1LN: C69.1, U7.40
ADC1LP: C70.1, U7.39
ADC2LN: C71.1, U7.44
ADC2LP: C72.1, U7.43
AGND: C3.2, C5.2, C29.2, C30.2, C31.2, C32.2, C37.2, C38.2, C47.2, C48.2, C49.2, C50.2, C51.2, C52.2, C53.2, C54.2, C55.2, C56.2, C57.2, C58.2, C59.2, C60.2, C73.1, C74.1, C75.1, C76.1, C77.1, C78.1, C79.1, C80.1, FB4.2, J14.2, J14.4, J14.6, J14.8, J14.10, J14.12, J14.14, J14.16, J14.18, J14.20, J17.1, R7.1, U4.11, U7.1, U7.4, U7.32, U7.34, U7.36
AIN1L: C63.2, J14.17
AIN1R: C66.2, J14.19
AOUT1L: C46.1, C47.1, R37.2
AOUT1R: C45.1, C48.1, R38.2
AOUT2L: C44.2, J14.5
AOUT2R: C43.1, C50.1, R40.2
AOUT3L: C42.2, J14.9
AOUT3R: C41.1, C52.1, R42.2
AOUT4L: C40.1, C53.1, R43.2
AOUT4R: C39.1, C54.1, R44.2
APDN: J13.9, U3.70, U7.10
BCLK: J13.6, U3.11, U7.17, U7.21
BLUE_LED: R54.1, U3.31
CC1: J16.A5, R50.2
CC2: J16.B5, R49.2
CM_1.5V: C55.1, U4.3, U4.5, U4.10, U4.12, U7.38
DBUG: J3.1, U3.72
DGND: C1.2, C2.2, C4.2, C6.2, C7.2, C8.2, C9.2, C10.2, C11.2, C12.2, C13.2, C14.2, C15.2, C16.2, C17.2, C18.2, C19.2, C20.2, C21.2, C22.2, C23.2, C24.2, C25.2, C26.2, C27.2, C28.2, C36.2, C62.2, FB4.1, J2.1, J2.2, J4.1, J9.3, J9.5, J9.9, J10.2, J10.4, J10.6, J10.8, J10.10, J10.12, J10.14, J10.16, J11.2, J11.4, J11.6, J11.8, J11.10, J11.12, J11.14, J11.16, J13.10, J15.4, J16.GND, J16.GND2, J18.6, JP7.GND, JP7.GND1, JP7.GND3, R2.1, R8.1, R17.1, R49.1, R50.1, S1.1, S2.1, S3.1, S4.1, U3.3, U3.6, U3.7, U3.8, U3.10, U3.29, U3.67, U6.5, U7.12, U7.25, U8.1, U8.3, Y1.2, Y1.4
GREEN_LED: R53.1, U3.27
I2C_SCK: J4.4, R52.1, TP1.1, U3.55
I2C_SDA: J4.3, R51.1, TP2.1, U3.64
LF: C34.1, C35.1, U7.47
LRCK: J13.5, U3.12, U7.18, U7.22
MCLK: TP4.1, U3.15, U7.2
MIDI-IN-PIN4: J15.1, R45.1
MIDI-IN-PIN5: D3.A, J15.2, U6.3
MIDI-OUT-PIN4: J15.3, R47.1
MIDI-OUT-PIN5: J15.5, R46.2
MIN: R48.1, U3.75, U6.6
MOUT: U3.56, U8.2
unnamed: C7.1, U3.98, Y1.1
unnamed: C9.1, U3.99, Y1.3
unnamed: C19.1, FB1.1, U3.96
unnamed: C14.1, L1.2, U3.90
unnamed: C23.1, FB2.1, U3.86
unnamed: C33.2, C69.2, R14.2, R60.1, U4.8
unnamed: I2C0.3, R51.2
unnamed: J8.1, U3.30
unnamed: I2C0.1, R52.2
unnamed: C34.2, R5.2
unnamed: C63.1, R15.1
unnamed: C61.2, C70.2, R59.2, U4.7
unnamed: C68.2, C72.2, R63.2, U4.1
unnamed: C20.1, R17.2, U3.97
unnamed: C26.1, FB3.2, U3.9
unnamed: C39.2, J14.15
unnamed: C40.2, J14.13
unnamed: C41.2, J14.11
unnamed: C42.1, C51.1, R41.2
unnamed: C43.2, J14.7
unnamed: C75.2, R25.2, R37.1
unnamed: L1.1, R16.2
unnamed: R7.2, R11.1, U5.1
unnamed: R1.1, S1.3, S2.2
unnamed: C74.2, R44.1, R65.2
unnamed: C73.2, R43.1, R58.2
unnamed: R8.2, R12.1, U1.1
unnamed: C80.2, R42.1, R57.2
unnamed: C44.1, C49.1, R39.2
unnamed: C46.2, J14.1
unnamed: C45.2, J14.3
unnamed: J4.2, UNK3V3_QWIIC0.2
unnamed: D4.2, R53.2
unnamed: D4.3, R54.2
unnamed: D4.1, R55.2
unnamed: R46.1, U8.4
unnamed: C3.1, FB5.2, U5.3
unnamed: C56.1, U7.35
unnamed: C61.1, R59.1, R60.2, U4.6
unnamed: C33.1, R14.1, R15.2, U4.9
unnamed: C79.2, R41.1, R56.2
unnamed: C78.2, R28.2, R40.1
unnamed: C76.2, R26.2, R38.1
unnamed: C77.2, R27.2, R39.1
unnamed: C67.2, C71.2, R61.2, R64.1, U4.14
unnamed: C66.1, R62.1
unnamed: C68.1, R63.1, R64.2, U4.2
unnamed: C67.1, R61.1, R62.2, U4.13
unnamed: Q1.1, R2.2
NRESET: C1.1, J9.10, R1.2, R3.1, R10.1, TP9.1, U3.58
OL1: R25.1, U7.28
OL2: R27.1, U7.30
OL3: R56.1, U7.6
OL4: R58.1, U7.8
OR1: R26.1, U7.29
OR2: R28.1, U7.31
OR3: R57.1, U7.7
OR4: R65.1, U7.9
RED_LED: R55.1, U3.25
REGINPUTS: C4.1, D1.C, FB5.1, Q1.2, U1.3
RXD: J18.3, U3.51
SDCD: JP7.CD1, JP7.CD2, R18.1, U3.49
SDCLK: JP7.SCLK, U3.40
SDCMD: JP7.DI, R23.1, U3.79
SDD0: JP7.DO, R21.1, U3.82
SDD1: JP7.RSV2, R22.1, U3.83
SDD2: JP7.RSV1, R19.1, U3.42
SDD3: JP7.CS, R20.1, U3.50
SHIELD: J16.SHLD1, J16.SHLD2, J16.SHLD3, J16.SHLD4, J16.SHLD5, J16.SHLD6, J16.SHLD7, J16.SHLD8
SPI0_CIPO: J13.3, U3.45, U7.24
SPI0_COPI: J13.4, U3.43, U7.23
SPI0_NPCS1: J13.2, R4.1, U3.35, U7.27
SPI0_SPCK: J13.1, U3.41, U7.26
SWCLK/TCK: J9.4, R9.1, TP6.1, U3.63
SWDIO/TMS: J9.2, R6.1, TP5.1, U3.57
TDI: J9.8, TP8.1, U3.74
TDMI: J13.7, U3.46, U7.20
TDMO: J13.8, U3.36, U7.16
TDO: J9.6, TP7.1, U3.77
TXD: J18.2, U3.23
UIA1: J10.7, U3.17
UIA2: J10.5, U3.20
UIA3: J10.3, U3.21
UIA4: J10.1, U3.16
UID1: J11.15, U3.65
UID2: J11.13, U3.69
UID3: J11.11, U3.78
UID4: J11.9, U3.80
UID5: J11.7, U3.84
UID6: J11.5, U3.85
UID7: J11.3, U3.87
UID8: J11.1, U3.88
UID9: J10.15, U3.89
UID10: J10.13, U3.91
UID11: J10.11, U3.92
UID12: J10.9, U3.1
USERSW: S3.3, S4.2, U3.26
VCCA: C5.1, C29.1, C30.1, C31.1, C32.1, C35.2, C37.1, C38.1, C57.1, C58.1, C59.1, C60.1, J6.1, R5.1, R11.2, U4.4, U5.2, U5.4, U7.5, U7.33, U7.37, U7.48
VDDOUT: C17.1, C18.1, C21.1, C22.1, C24.1, C25.1, FB1.2, FB2.2, U3.4, U3.18, U3.22, U3.39, U3.76
VIN: J1.1, J1.2, Q1.3
V_USB: C2.1, D1.A, J16.VBUS1, J16.VBUS2
